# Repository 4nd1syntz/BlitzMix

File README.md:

# BlitzMix
An 8-channel mono/stereo mixer that works with 4 subgroups and two main FX.

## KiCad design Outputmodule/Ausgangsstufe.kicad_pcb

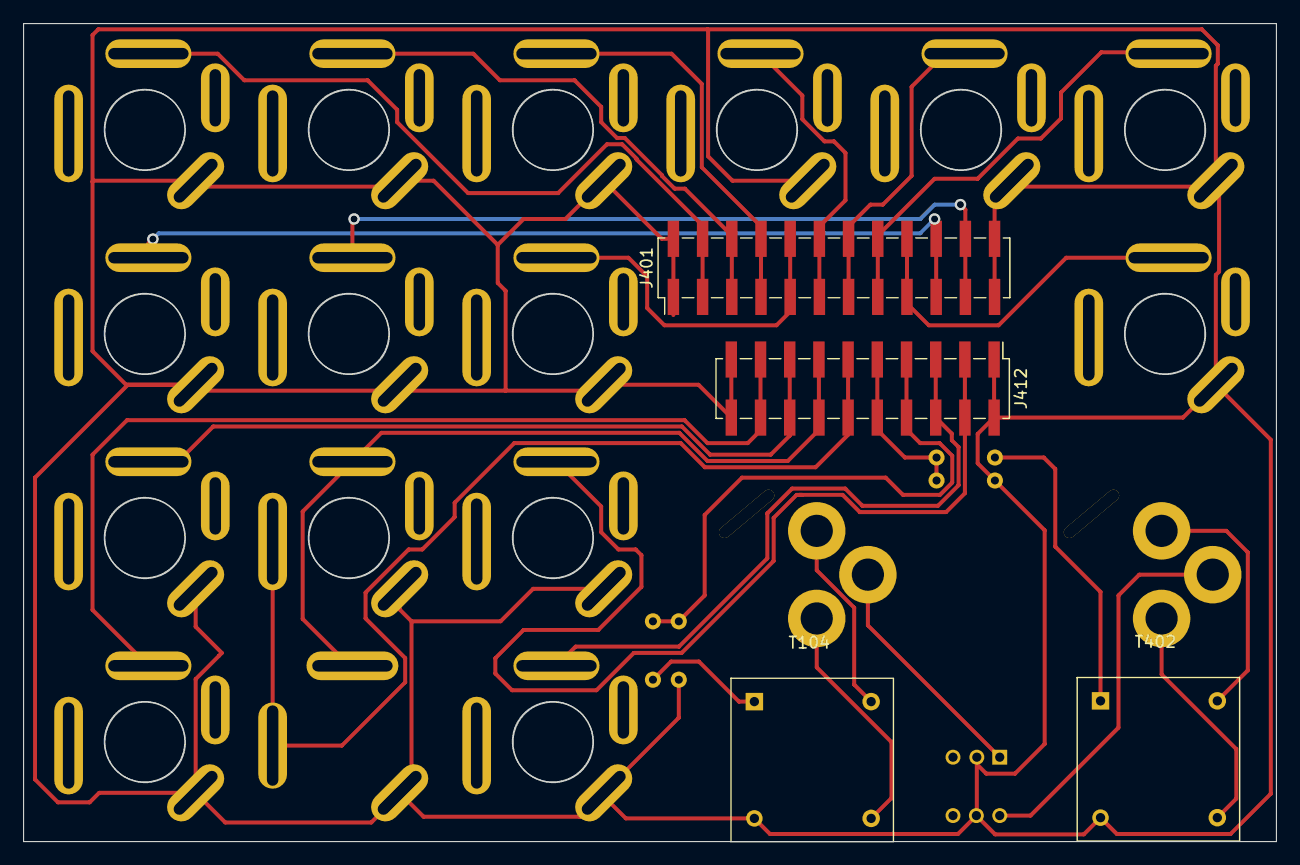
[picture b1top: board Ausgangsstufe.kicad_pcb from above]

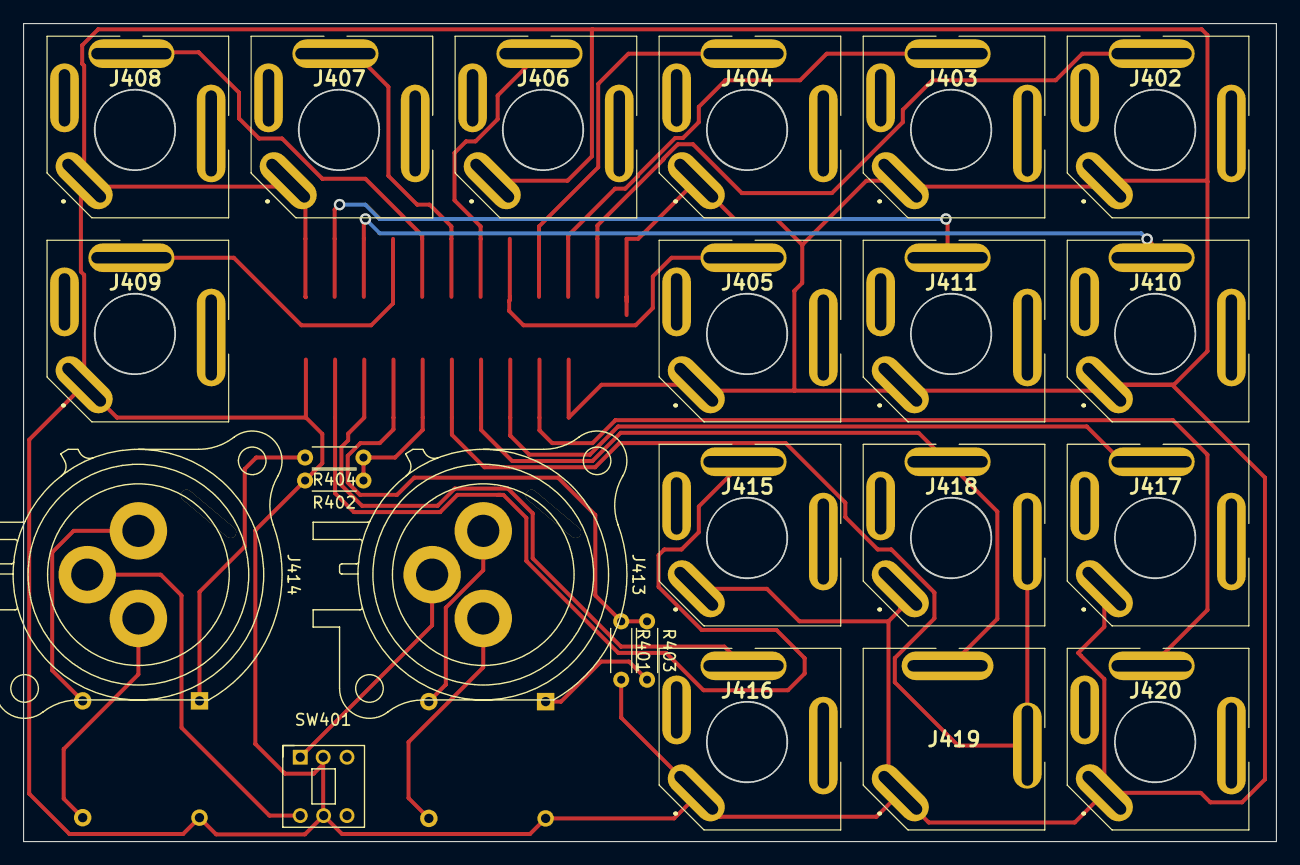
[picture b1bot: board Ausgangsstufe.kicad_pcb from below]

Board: 2 copper layers, 109.0 x 71.2 mm, 27 parts (23 on the bottom side), 27 nets.

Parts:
J401: CH 1-10; PinHeader_2x12_P2.54mm_Vertical_SMD
J402: Dir Out 1; ACJSMV344 flat solder 6,3mm
J403: Dir Out 2; ACJSMV344 flat solder 6,3mm
J404: Dir Out 3R; ACJSMV344 flat solder 6,3mm
J405: Dir Out 3L; ACJSMV344 flat solder 6,3mm
J406: Dir Out 4; ACJSMV344 flat solder 6,3mm
J407: Dir Out 5; ACJSMV344 flat solder 6,3mm
J408: Dir Out 6R; ACJSMV344 flat solder 6,3mm
J409: Dir Out 6L; ACJSMV344 flat solder 6,3mm
J410: Dir Out 7; ACJSMV344 flat solder 6,3mm
J411: Dir Out 8; ACJSMV344 flat solder 6,3mm
J412: Ausgänge; PinHeader_2x10_P2.54mm_Vertical_SMD
J413: XLR Rechts; Jack_XLR_Neutrik_NC3FAAV1-DA_Vertical
J414: XLR Links; Jack_XLR_Neutrik_NC3FAAV1-DA_Vertical
J415: 6,3Klinke R; ACJSMV344 flat solder 6,3mm
J416, J417, J420: AudioJack2_Switch; ACJSMV344 flat solder 6,3mm
J418: AudioJack3; ACJSMV344 flat solder 6,3mm
J419: Kopfhörer; ACJS-MV35-3 flat solder
R401, R402, R403, R404: ?; R_Axial_DIN0204_L3.6mm_D1.6mm_P5.08mm_Horizontal
SW401: Gnd Left; SW -- Latching_mini_SW
T104: XLR Rechts; Transformer 102D
T402: XLR Links; Transformer 102D

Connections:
CH1: J401.3, J401.4, J402.4
CH2: J401.5, J401.6, J403.4
CH3: J401.7, J401.8, J404.4
CH4: J401.9, J401.10, J405.4
CH5: J401.11, J401.12, J406.4
CH6: J401.13, J401.14, J407.4
CH7: J401.15, J401.16, J408.4
CH8: J401.17, J401.18, J409.4
CH9: J401.19, J401.20, J410.4
CH10: J401.21, J401.22, J411.4
GND: J401.1, J401.2, J401.23, J401.24, J402.1, J403.1, J404.1, J405.1, J406.1, J407.1, J408.1, J409.1, J410.1, J411.1, J412.1, J412.2, J412.19, J412.20, J415.1, J416.1, J417.1, J418.1, J419.1, J420.1, R401.2, R402.2, SW401.2 (B), SW401.5 (B), T104.2 (AB), T402.2 (AB)
Klinke L: J412.5, J412.6, J416.4
Klinke R: J412.3, J412.4, J415.4
Kopfhörer L: J412.11, J412.12, J418.3, J419.3
Kopfhörer R: J412.13, J412.14, J418.4, J419.4
Main L: J412.9, J412.10, R402.1, R404.1
Main R: J412.7, J412.8, R401.1, R403.1
unnamed: J413.1, T104.5 (SA)
unnamed: J413.2, T104.3 (SB)
unnamed: J413.3, SW401.1 (A)
unnamed: J414.1, T402.5 (SA)
unnamed: J414.2, T402.3 (SB)
unnamed: J414.3, SW401.4 (A)
unnamed: R403.2, T104.1 (AA)
unnamed: R404.2, T402.1 (AA)
Rec L: J412.17, J412.18, J420.4
Rec R: J412.15, J412.16, J417.4

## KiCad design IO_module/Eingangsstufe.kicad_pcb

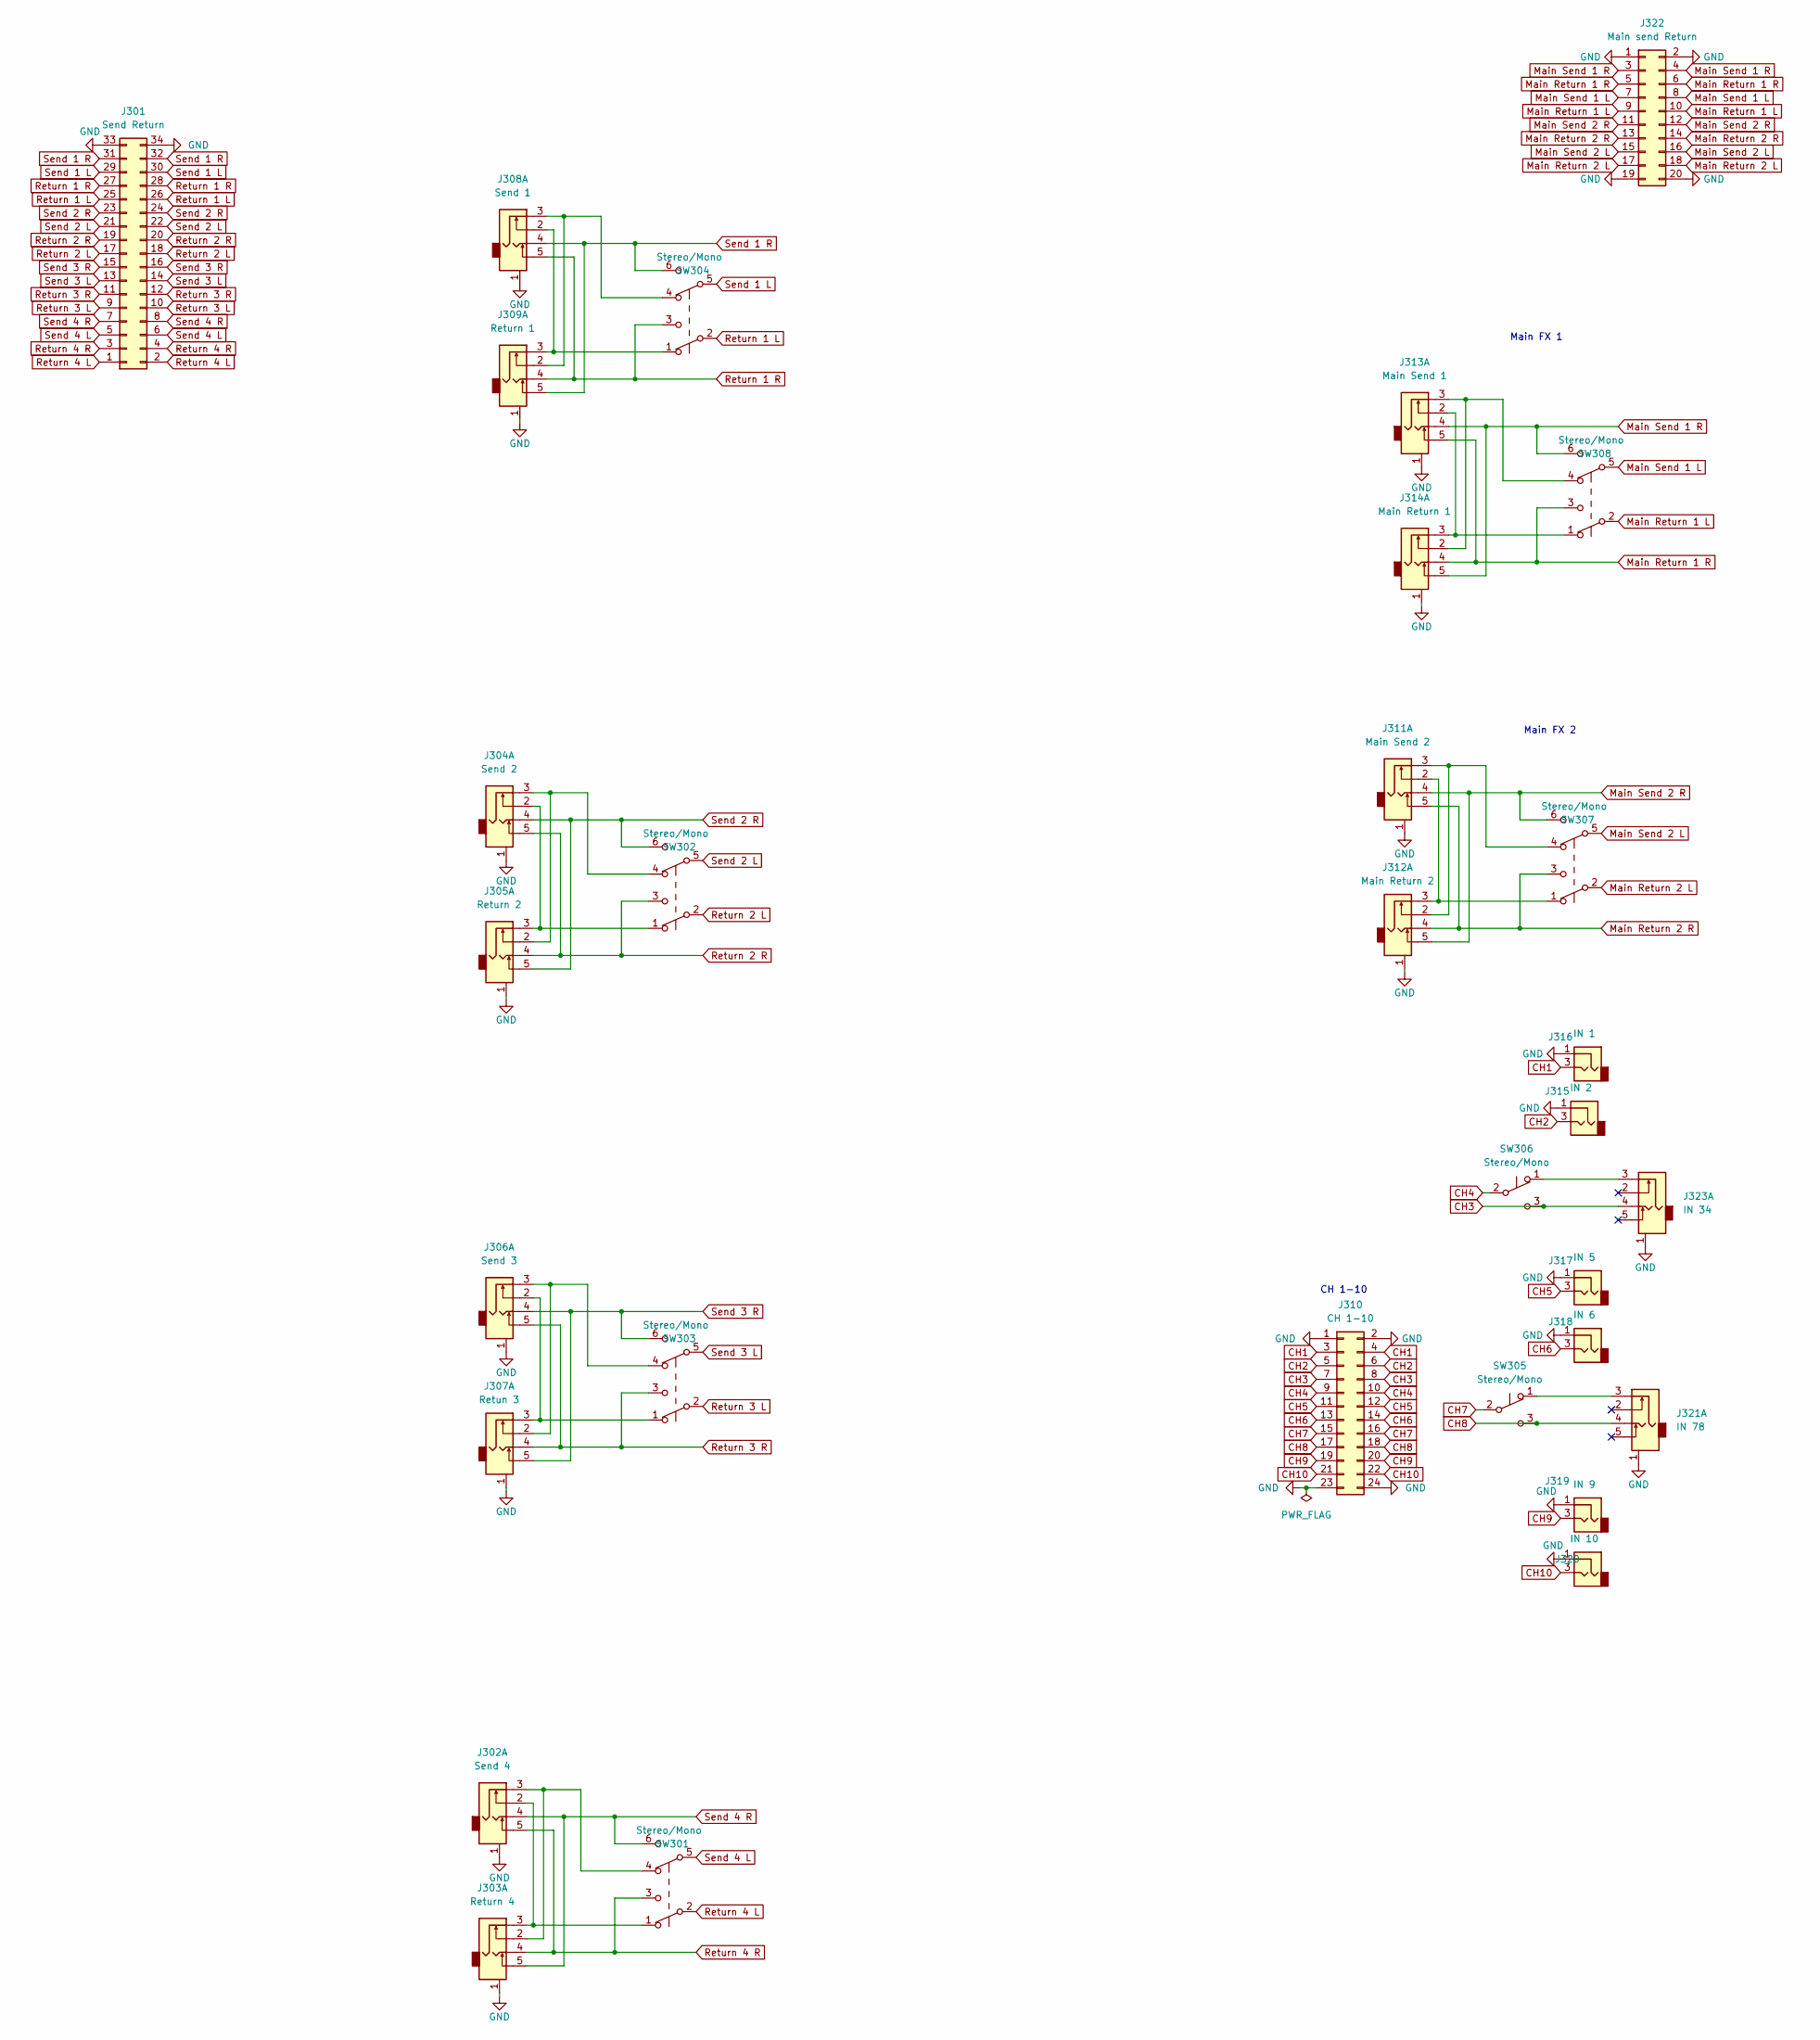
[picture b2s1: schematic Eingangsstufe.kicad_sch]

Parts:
J301: Send Return; PinSocket_2x17_P2.54mm_Vertical
J302: Send 4; ACJSMV355 flat solder
J303: Return 4; ACJSMV355 flat solder
J304: Send 2; ACJSMV355 flat solder
J305: Return 2; ACJSMV355 flat solder
J306: Send 3; ACJSMV355 flat solder
J307: Retun 3; ACJSMV355 flat solder
J308: Send 1; ACJSMV355 flat solder
J309: Return 1; ACJSMV355 flat solder
J310: CH 1-10; PinHeader_2x12_P2.54mm_Vertical
J311: Main Send 2; ACJSMV355 flat solder
J312: Main Return 2; ACJSMV355 flat solder
J313: Main Send 1; ACJSMV355 flat solder
J314: Main Return 1; ACJSMV355 flat solder
J315: IN 2; ACJSMV35-2 flat solder
J316: IN 1; ACJSMV35-2 flat solder
J317: IN 5; ACJSMV35-2 flat solder
J318: IN 6; ACJSMV35-2 flat solder
J319: IN 9; ACJSMV35-2 flat solder
J320: IN 10; ACJSMV35-2 flat solder
J321: IN 78; ACJS-MV35-3 flat solder
J322: Main send Return; PinHeader_2x09_P2.54mm_Vertical
J323: IN 34; ACJS-MV35-3 flat solder
SW301, SW302, SW303, SW304, SW305, SW306, SW307, SW308: Stereo/Mono; SW -- Latching_mini_SW

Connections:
CH1: J310.3, J310.4, J316.3
CH2: J310.5, J310.6, J315.3
CH3: J310.7, J310.8, J323.4, SW306.3 (C)
CH4: J310.9, J310.10, SW306.2 (B)
CH5: J310.11, J310.12, J317.3
CH6: J310.13, J310.14, J318.3
CH7: J310.15, J310.16, SW305.2 (B)
CH8: J310.17, J310.18, J321.4, SW305.3 (C)
CH9: J310.19, J310.20, J319.3
CH10: J310.21, J310.22, J320.3
GND: J301.33, J301.34, J302.1, J303.1, J304.1, J305.1, J306.1, J307.1, J308.1, J309.1, J310.1, J310.2, J310.23, J310.24, J311.1, J312.1, J313.1, J314.1, J315.1, J316.1, J317.1, J318.1, J319.1, J320.1, J321.1, J322.1, J322.2, J322.19, J322.20, J323.1
Main Return 1 L: J322.9, J322.10, SW308.2 (B)
Main Return 1 R: J313.5, J314.4, J322.5, J322.6, SW308.3 (C)
Main Return 2 L: J322.17, J322.18, SW307.2 (B)
Main Return 2 R: J311.5, J312.4, J322.13, J322.14, SW307.3 (C)
Main Send 1 L: J322.7, J322.8, SW308.5 (B)
Main Send 1 R: J313.4, J314.5, J322.3, J322.4, SW308.6 (C)
Main Send 2 L: J322.15, J322.16, SW307.5 (B)
Main Send 2 R: J311.4, J312.5, J322.11, J322.12, SW307.6 (C)
unnamed: J302.2, J303.3, SW301.1 (A)
unnamed: J302.3, J303.2, SW301.4 (A)
unnamed: J304.2, J305.3, SW302.1 (A)
unnamed: J304.3, J305.2, SW302.4 (A)
unnamed: J306.2, J307.3, SW303.1 (A)
unnamed: J306.3, J307.2, SW303.4 (A)
unnamed: J308.2, J309.3, SW304.1 (A)
unnamed: J308.3, J309.2, SW304.4 (A)
unnamed: J311.2, J312.3, SW307.1 (A)
unnamed: J311.3, J312.2, SW307.4 (A)
unnamed: J313.2, J314.3, SW308.1 (A)
unnamed: J313.3, J314.2, SW308.4 (A)
unnamed: J321.3, SW305.1 (A)
unnamed: J323.3, SW306.1 (A)
Return 1 L: J301.25, J301.26, SW304.2 (B)
Return 1 R: J301.27, J301.28, J308.5, J309.4, SW304.3 (C)
Return 2 L: J301.17, J301.18, SW302.2 (B)
Return 2 R: J301.19, J301.20, J304.5, J305.4, SW302.3 (C)
Return 3 L: J301.9, J301.10, SW303.2 (B)
Return 3 R: J301.11, J301.12, J306.5, J307.4, SW303.3 (C)
Return 4 L: J301.1, J301.2, SW301.2 (B)
Return 4 R: J301.3, J301.4, J302.5, J303.4, SW301.3 (C)
Send 1 L: J301.29, J301.30, SW304.5 (B)
Send 1 R: J301.31, J301.32, J308.4, J309.5, SW304.6 (C)
Send 2 L: J301.21, J301.22, SW302.5 (B)
Send 2 R: J301.23, J301.24, J304.4, J305.5, SW302.6 (C)
Send 3 L: J301.13, J301.14, SW303.5 (B)
Send 3 R: J301.15, J301.16, J306.4, J307.5, SW303.6 (C)
Send 4 L: J301.5, J301.6, SW301.5 (B)
Send 4 R: J301.7, J301.8, J302.4, J303.5, SW301.6 (C)

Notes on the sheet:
Main FX 2
CH 1-10
Main FX 1

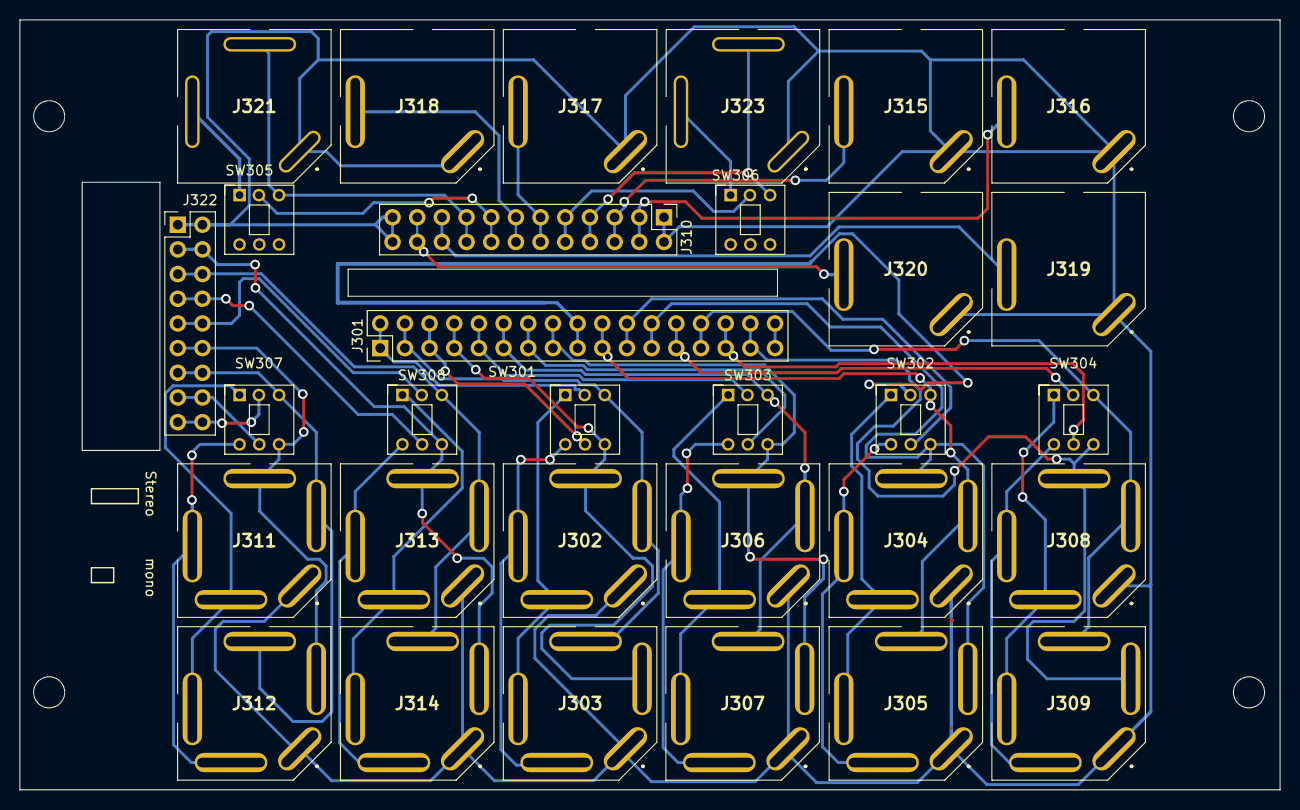
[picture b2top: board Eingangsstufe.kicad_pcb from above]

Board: 2 copper layers, 129.7 x 79.2 mm, 31 parts (0 on the bottom side), 49 nets.
